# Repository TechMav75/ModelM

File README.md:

# Model M to USB converter

This is a drop in replacement for the controller board on an IBM Model M keyboard, part number 1391401.

You will find Gerber files, controller files, and the BOM to build your own board.

The board is designed to accomodate 16/12 pin and 16/8/4 pin setups. You will need to check your keyboard controller to see which connectors you will need.

If you need the 16/8/4 pin style, install the 8pin Trio Mate in the left hand holes of the 12pin connector. The 4pin will go in the obvious place on the right of the board.

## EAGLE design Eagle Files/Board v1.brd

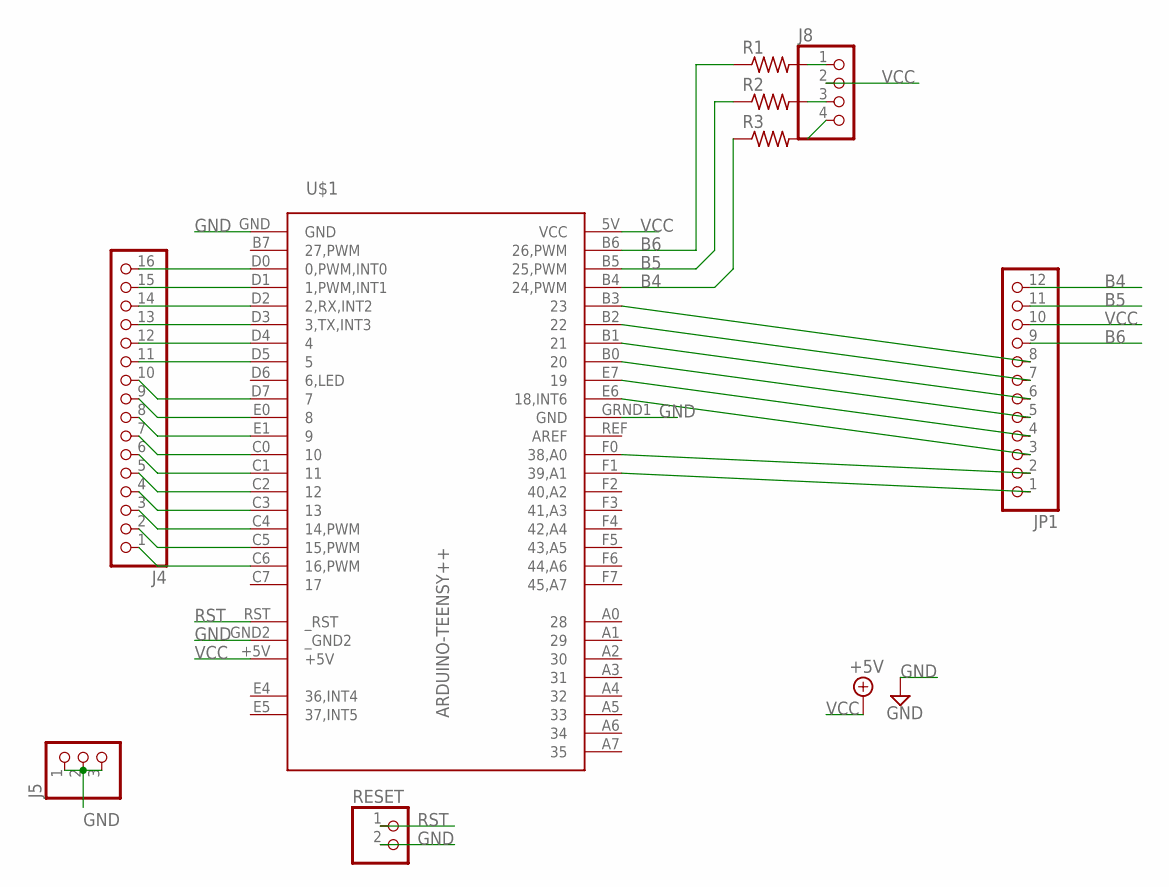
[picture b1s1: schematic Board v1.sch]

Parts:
J4: PINHD-1X16; 1X16
J5: PINHD-1X3; 1X03
J8: PINHD-1X4; 1X04
JP1: PINHD-1X12; 1X12
R1, R2, R3: R-US_R0805; R0805
RESET: PINHD-1X2; 1X02
U$1: ARDUINO-TEENSY++; TEENSY++

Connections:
B4: JP1.12, R3.1, U$1.B4 (24,PWM)
B5: JP1.11, R2.1, U$1.B5 (25,PWM)
B6: JP1.9, R1.1, U$1.B6 (26,PWM)
GND: J5.1, J5.2, J5.3, RESET.2, U$1.GND, U$1.GND2 (_GND2), U$1.GRND1 (GND)
unnamed: J4.16, U$1.D0 (0,PWM,INT0)
unnamed: J8.1, R1.2
unnamed: J8.3, R2.2
unnamed: J8.4, R3.2
unnamed: J4.15, U$1.D1 (1,PWM,INT1)
unnamed: J4.14, U$1.D2 (2,RX,INT2)
unnamed: J4.13, U$1.D3 (3,TX,INT3)
unnamed: J4.12, U$1.D4 (4)
unnamed: J4.11, U$1.D5 (5)
unnamed: J4.10, U$1.D7 (7)
unnamed: J4.9, U$1.E0 (8)
unnamed: J4.8, U$1.E1 (9)
unnamed: J4.7, U$1.C0 (10)
unnamed: J4.6, U$1.C1 (11)
unnamed: J4.5, U$1.C2 (12)
unnamed: J4.4, U$1.C3 (13)
unnamed: J4.3, U$1.C4 (14,PWM)
unnamed: J4.2, U$1.C5 (15,PWM)
unnamed: J4.1, U$1.C6 (16,PWM)
unnamed: JP1.8, U$1.B3 (23)
unnamed: JP1.7, U$1.B2 (22)
unnamed: JP1.6, U$1.B1 (21)
unnamed: JP1.5, U$1.B0 (20)
unnamed: JP1.4, U$1.E7 (19)
unnamed: JP1.3, U$1.E6 (18,INT6)
unnamed: JP1.2, U$1.F0 (38,A0)
unnamed: JP1.1, U$1.F1 (39,A1)
RST: RESET.1, U$1.RST (_RST)
VCC: J8.2, JP1.10, U$1.5V (VCC), U$1.+5V

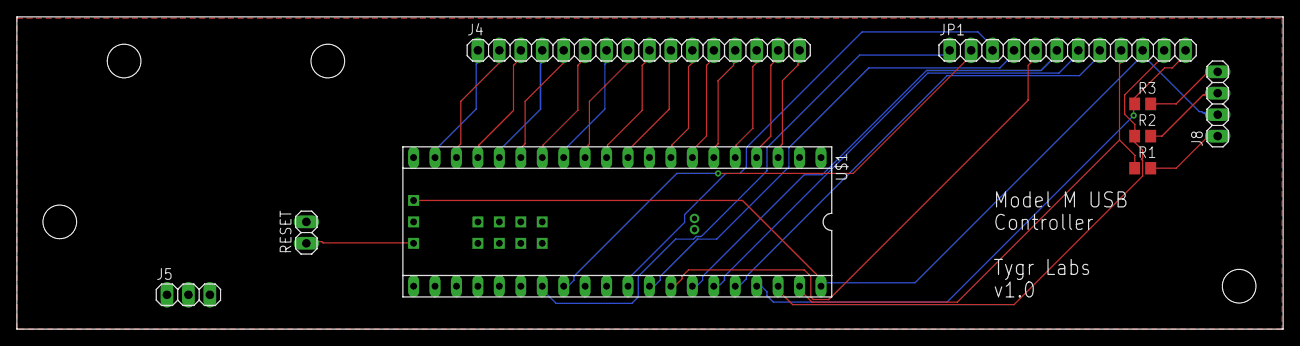
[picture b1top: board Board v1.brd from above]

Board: 2 copper layers, 150.0 x 37.0 mm, 9 parts (0 on the bottom side), 33 nets.

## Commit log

2018-06-29 Updated board to include flood fill on ground planes.
2018-07-04 Modified schematic and board for 16/12 and 16/8/4 pin connector setups.
